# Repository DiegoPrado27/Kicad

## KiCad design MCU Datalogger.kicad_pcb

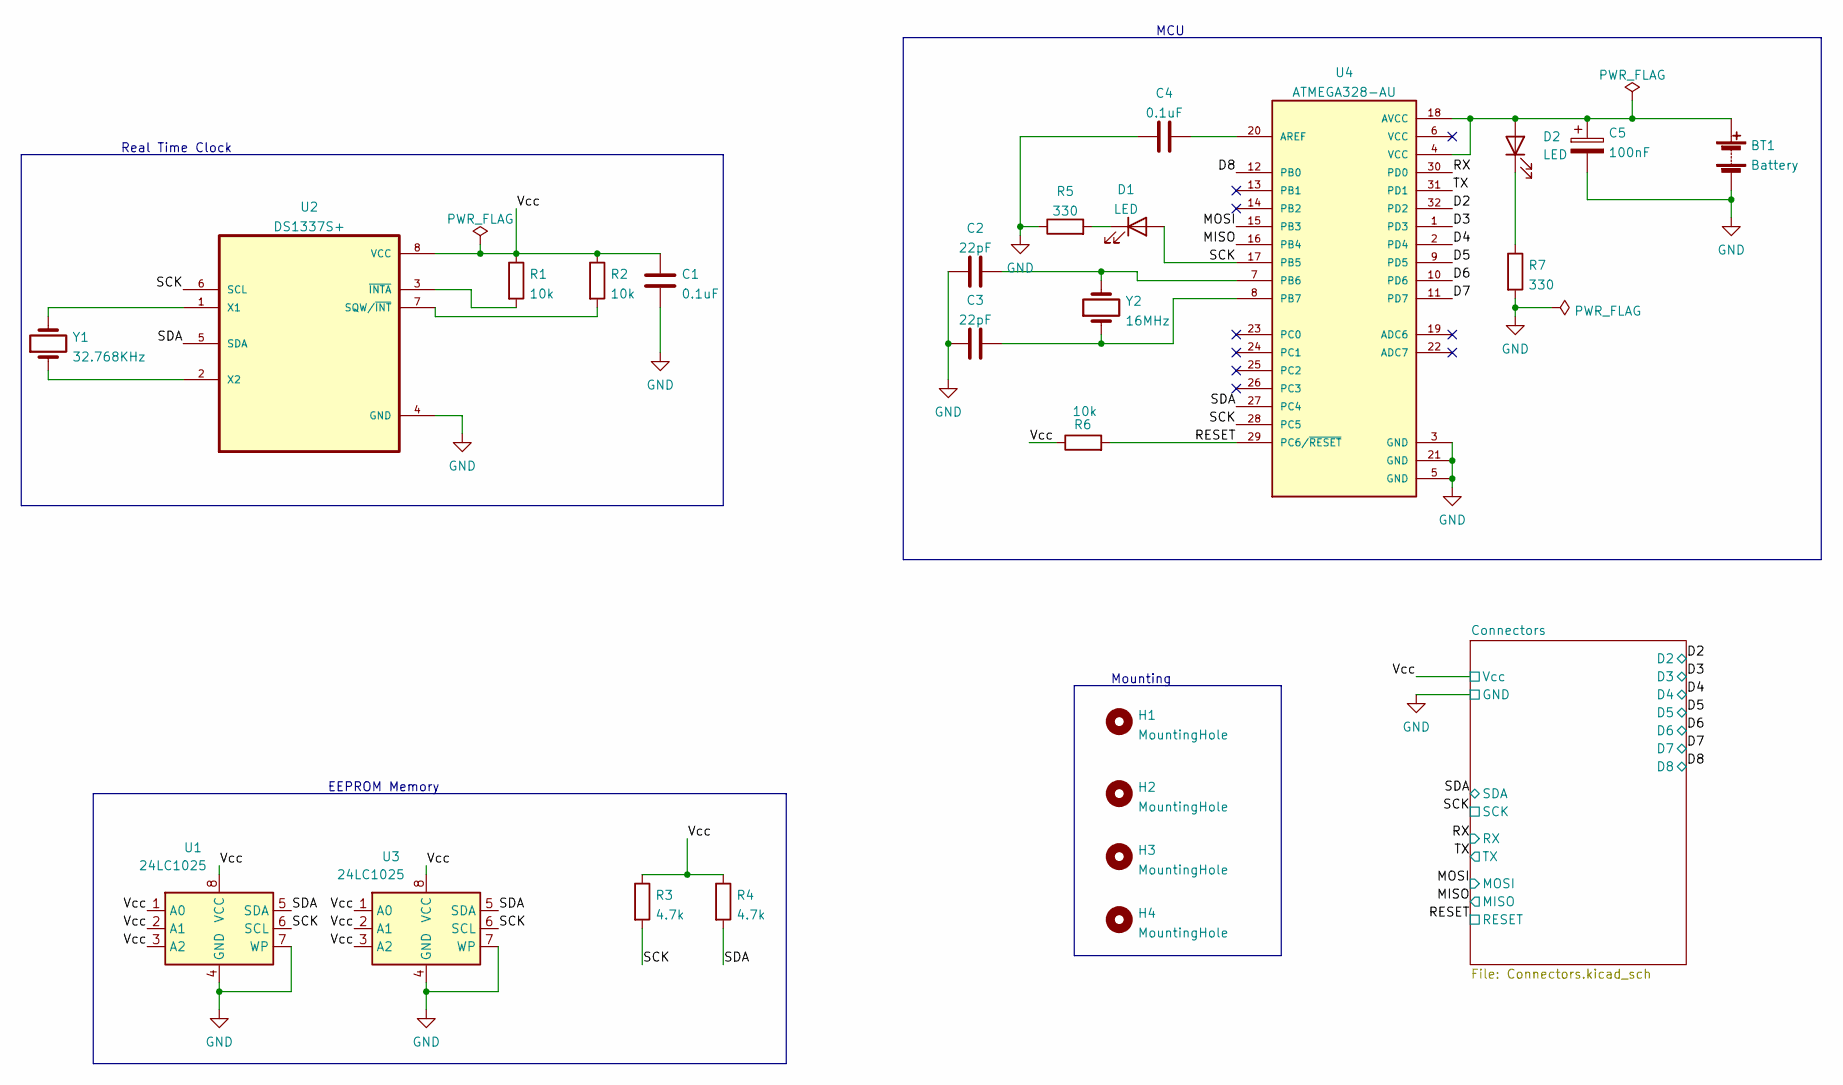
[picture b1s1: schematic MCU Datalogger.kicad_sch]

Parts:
BT1: Battery; PinHeader_1x02_P2.54mm_Vertical
C1, C4: 0.1uF; C_0805_2012Metric
C2, C3: 22pF; C_0805_2012Metric
C5: 100nF; C_0805_2012Metric
D1, D2: LED; LED_0805_2012Metric
H1, H2, H3, H4: MountingHole; MountingHole_2.1mm
R1, R2, R6: 10k; R_0805_2012Metric
R3, R4: 4.7k; R_0805_2012Metric
R5, R7: 330; R_0805_2012Metric
U1, U3: 24LC1025; SOIC-8_5.23x5.23mm_P1.27mm
U2: DS1337S+; SOIC127P600X175-8N
U4: ATMEGA328-AU; QFP80P900X900X120-32N
Y1: 32.768KHz; Crystal_SMD_5032-2Pin_5.0x3.2mm_HandSoldering
Y2: 16MHz; Crystal_SMD_5032-2Pin_5.0x3.2mm_HandSoldering

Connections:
/D2: U4.32 (PD2); also elsewhere on the board
/D3: U4.1 (PD3); also elsewhere on the board
/D4: U4.2 (PD4); also elsewhere on the board
/D5: U4.9 (PD5); also elsewhere on the board
/D6: U4.10 (PD6); also elsewhere on the board
/D7: U4.11 (PD7); also elsewhere on the board
/D8: U4.12 (PB0); also elsewhere on the board
/MISO: U4.16 (PB4); also elsewhere on the board
/MOSI: U4.15 (PB3); also elsewhere on the board
/RESET: R6.2, U4.29 (PC6/~RESET); also elsewhere on the board
/RX: U4.30 (PD0); also elsewhere on the board
/SCK: D1.2 (A), R3.2, U1.6 (SCL), U2.6 (SCL), U3.6 (SCL), U4.17 (PB5), U4.28 (PC5); also elsewhere on the board
/SDA: R4.2, U1.5 (SDA), U2.5 (SDA), U3.5 (SDA), U4.27 (PC4); also elsewhere on the board
/TX: U4.31 (PD1); also elsewhere on the board
/Vcc: C1.1, R1.1, R2.1, R3.1, R4.1, R6.1, U1.1 (A0), U1.2 (A1), U1.3 (A2), U1.8 (VCC), U2.8 (VCC), U3.1 (A0), U3.2 (A1), U3.3 (A2), U3.8 (VCC); also elsewhere on the board
GND: BT1.2 (-), C1.2, C2.1, C3.1, C4.1, C5.2, R5.1, R7.2, U1.4 (GND), U1.7 (WP), U2.4 (GND), U3.4 (GND), U3.7 (WP), U4.3 (GND), U4.5 (GND), U4.21 (GND); also elsewhere on the board
unnamed: C2.2, U4.7 (PB6), Y2.2
unnamed: D2.1 (K), R7.1
unnamed: R1.2, U2.3 (~INTA)
unnamed: D1.1 (K), R5.2
unnamed: R2.2, U2.7 (SQW/~INT)
unnamed: BT1.1 (+), C5.1, D2.2 (A), U4.4 (VCC), U4.18 (AVCC)
unnamed: C4.2, U4.20 (AREF)
unnamed: U2.2 (X2), Y1.1
unnamed: U2.1 (X1), Y1.2
unnamed: C3.2, U4.8 (PB7), Y2.1

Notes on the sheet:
EEPROM Memory
Mounting
Real Time Clock
MCU

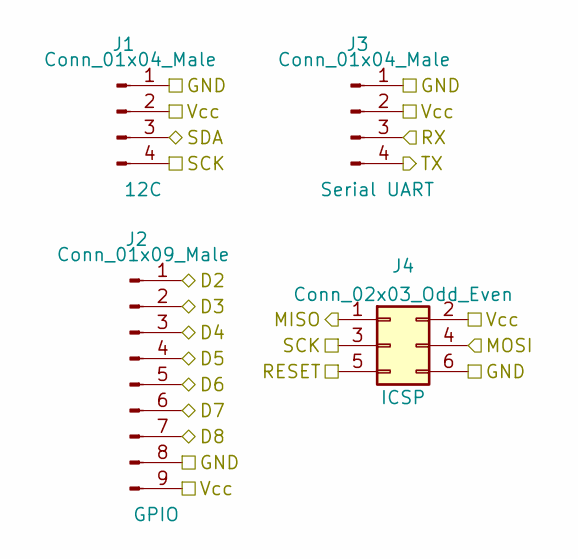
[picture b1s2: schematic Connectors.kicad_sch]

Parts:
J1, J3: Conn_01x04_Male; PinHeader_1x04_P2.54mm_Vertical
J2: Conn_01x09_Male; PinHeader_1x09_P2.54mm_Vertical
J4: Conn_02x03_Odd_Even; PinHeader_2x03_P2.54mm_Vertical

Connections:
/D2: J2.1; also elsewhere on the board
/D3: J2.2; also elsewhere on the board
/D4: J2.3; also elsewhere on the board
/D5: J2.4; also elsewhere on the board
/D6: J2.5; also elsewhere on the board
/D7: J2.6; also elsewhere on the board
/D8: J2.7; also elsewhere on the board
/MISO: J4.1; also elsewhere on the board
/MOSI: J4.4; also elsewhere on the board
/RESET: J4.5; also elsewhere on the board
/RX: J3.3; also elsewhere on the board
/SCK: J1.4, J4.3; also elsewhere on the board
/SDA: J1.3; also elsewhere on the board
/TX: J3.4; also elsewhere on the board
/Vcc: J1.2, J2.9, J3.2, J4.2; also elsewhere on the board
GND: J1.1, J2.8, J3.1, J4.6; also elsewhere on the board

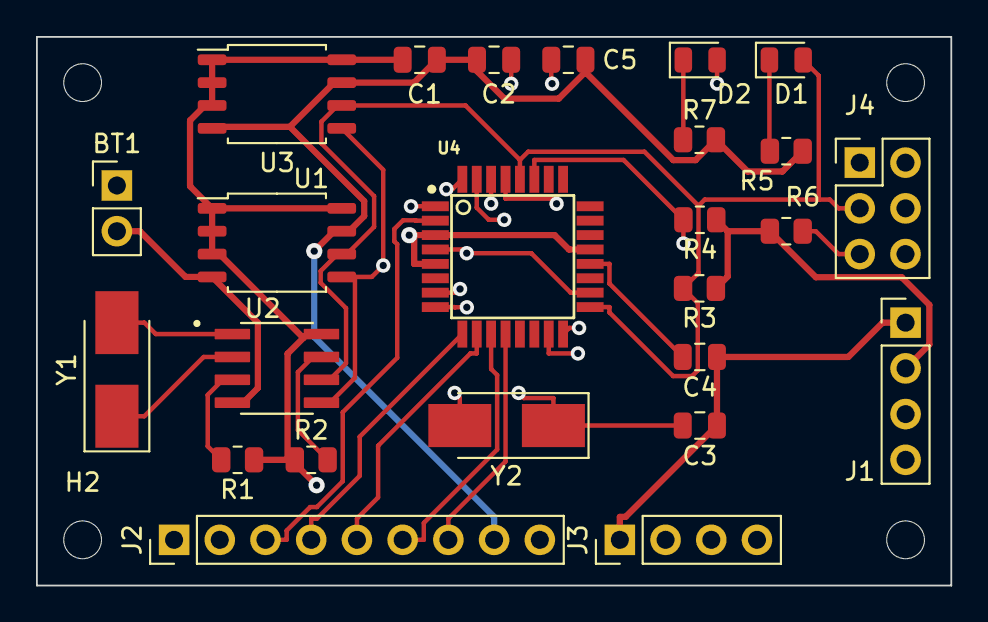
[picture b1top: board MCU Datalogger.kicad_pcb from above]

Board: 4 copper layers, 50.8 x 30.5 mm, 29 parts (0 on the bottom side), 26 nets.

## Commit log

2022-01-13 First commit of new project
2022-01-13 setup
2022-01-13 Have added required symbols to the schematic sheets
2022-01-13 Changed locations of symbols
2022-01-13 Added component values
2022-01-14 Completed symbol-footprint associations
2022-01-14 Wiring
2022-01-14 final Wiring
2022-01-14 Nets
2022-01-14 comments
2022-01-14 setup pcbnew
2022-01-14 PCB footprint placement
2022-01-14 rooting
2022-01-14 silk
2022-01-14 4layer
2022-01-14 router
2022-01-14 error
    git commit -amerror
2022-01-14 route
    git commit -am route
2022-01-14 routing
